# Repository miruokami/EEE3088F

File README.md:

# Micro-mouse Project
## Project Overview
The Micro-mouse project focuses on designing and building subassemblies for a simplified micro-mouse, a maze-solving robot. 
This project involves creating hardware components with some minor software aspects, adhering to a strict budget.

## Project Modules
### Provided Modules
Motherboard: Connects all the PCBs together, serving as the base for other modules.
Processor: A STM32xxx processor board.

### Modules to Design and Manufacture
#### Power Module:
Responsibilities: Powering the entire system, running the motors, and charging the battery.
Requirements: Fit onto the motherboard pin headers, appropriate size for the robot, includes necessary connectors (e.g., JST PH 2mm pitch for the battery, 2x8 pin header for motherboard connection).

#### Sensor Module:
Responsibilities: Detecting and sensing objects.
Requirements: Fit onto the motherboard pin headers, appropriate size for the robot, utilize hysteresis for sensing, accurately sense different maze wall configurations.

## Demonstration Procedures
### Sensing Subsystem
Preparation: Bring a PCB, code ready to flash onto the STM32F0, and populated PCB.
Setup: Flash code, connect the necessary wires, plug sensing PCB into the testing PCB.
Testing: The sensor is supplied with power, and walls will be moved in various configurations to test the sensing accuracy.

### Power Subsystem
Preparation: Bring a PCB, and 4 spare PCBs.
Setup: Plug power PCB into the testing jig.

This README provides a concise overview of the Micro-mouse project, including project modules, and demonstration procedures. 
For comprehensive guidelines, please refer to the provided project description document .

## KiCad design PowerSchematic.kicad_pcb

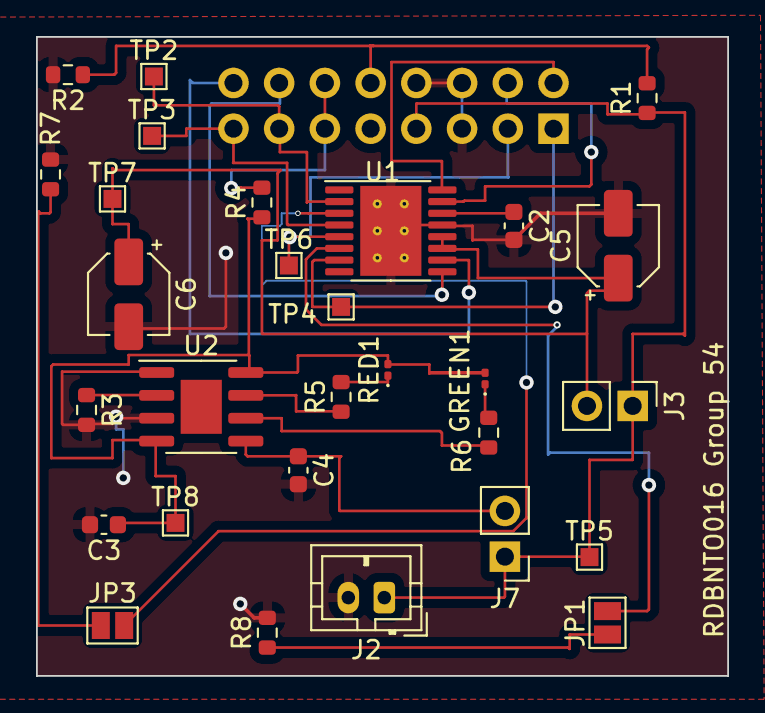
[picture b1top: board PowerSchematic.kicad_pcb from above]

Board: 2 copper layers, 38.4 x 35.5 mm, 30 parts (1 on the bottom side), 25 nets.

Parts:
C2: 2.2uF; C_0603_1608Metric
C3: 100nF; C_0603_1608Metric
C4: 10uF; C_0603_1608Metric
C5: 10uF; CP_Elec_4x3
C6: 0.01uF; CP_Elec_4x3
GREEN1: LED; LED_0201_0603Metric
J1: Conn_02x08_Odd_Even; PinHeader_2x08_P2.54mm_Vertical
J2: Battery; JST_PH_B2B-PH-K_1x02_P2.00mm_Vertical
J3, J7: Conn_01x02_Pin; PinHeader_1x02_P2.54mm_Vertical
JP1, JP3: SolderJumper_2_Open; SolderJumper-2_P1.3mm_Open_Pad1.0x1.5mm
R1: 10k; R_0603_1608Metric
R2: 5k; R_0603_1608Metric
R3: 1.2k; R_0603_1608Metric
R4: 0.4; R_0603_1608Metric
R5, R6: 1k; R_0603_1608Metric
R7, R8: 1; R_0603_1608Metric
RED1: LED; LED_0201_0603Metric
TP2, TP3, TP4, TP5, TP6, TP7, TP8: TestPoint; TestPoint_Pad_1.0x1.0mm
U1: DRV8833PWP; HTSSOP-16-1EP_4.4x5mm_P0.65mm_EP3.4x5mm_Mask2.46x2.31mm_The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
U2: TP4056; SOIC-8-1EP_3.9x4.9mm_P1.27mm_EP2.29x3mm

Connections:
5V: J1.11, J1.12, R4.2
BATT+: J1.7, J2.1, J3.1, J7.1, R1.1, TP5.1
BATT-: C2.2, C3.2, C4.2, C5.2, C6.2, J1.5, J1.6, J1.8, J2.2, R2.2, R3.2, R7.2, R8.2, U1.13 (GND), U1.17 (GND(PPAD)), U2.1 (TEMP), U2.3 (GND)
BATT_ADC: J1.10, R1.2, R2.1
Motor1_A: J1.13, TP2.1, U1.2 (AOUT1)
Motor1_B: J1.15, TP3.1, U1.4 (AOUT2)
Motor2_A: J1.1, TP4.1, U1.7 (BOUT1)
Motor2_B: J1.3, TP6.1, U1.5 (BOUT2)
unnamed: C3.1, GREEN1.2 (A), R4.1, RED1.2 (A), TP8.1, U2.4 (VCC), U2.8 (CE)
unnamed: GREEN1.1 (K), R6.2
unnamed: C4.1, J7.2, U2.5 (BAT)
unnamed: JP1.1 (A), R8.1
unnamed: JP1.2 (B), U1.6 (BISEN)
unnamed: JP3.1 (A), R7.1
unnamed: JP3.2 (B), U1.3 (AISEN)
unnamed: R5.2, RED1.1 (K)
unnamed: C2.1, U1.14 (VINT)
unnamed: R3.1, U2.2 (PROG)
unnamed: R5.1, U2.7 (~CHRG)
unnamed: R6.1, U2.6 (~STDBY)
PC6: J1.2, U1.16 (AIN1)
PC7: J1.4, U1.15 (AIN2)
PC8: J1.14, U1.9 (BIN1)
PC9: J1.16, U1.10 (BIN2)
VM: C5.1, C6.1, J3.2, TP7.1, U1.11 (VCP), U1.12 (VM)

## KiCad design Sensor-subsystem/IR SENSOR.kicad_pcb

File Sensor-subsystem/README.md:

# Robot Sensor Subsystem
## Overview
This repository contains the design, implementation, and integration details of the sensor subsystem for a robot project. The sensor subsystem is responsible for detecting obstacles in front, to the left, and to the right of the robot, providing essential information for navigation and obstacle avoidance.

## Features
Obstacle Detection: Uses IR sensors to detect obstacles in three directions: front, left, and right.
Power Management: Implements MOSFET switches to enable/disable sensors, conserving battery power when sensors are not in use.
Visual Indication: Uses LEDs on the processor board to indicate the presence of obstacles.
High Reliability: Designed with redundant ground planes, decoupling capacitors, and other failure management processes to ensure robust operation.

## System Integration
The sensor subsystem integrates with the main robot system through a 2x14 pin header connection. It interfaces with the robot's processor to provide obstacle detection data and receive power management signals.

## Power Management
To ensure efficient power usage, the subsystem employs MOSFET switches controlled by PWM signals from the processor. This allows the sensors to be powered only when needed, conserving battery life.

## Components
IR Sensors: Detect obstacles by emitting and detecting infrared light.
MOSFETs: Switch the power supply to the sensors on and off.
Microcontroller: Reads sensor data and controls MOSFETs and LEDs.
LEDs: Indicate the presence of obstacles.

## Software
The software interfaces the sensor subsystem with the rest of the robot's system, handling sensor readings, power management, and LED indications.

## Getting Started
Hardware Setup: Assemble the sensor subsystem on the PCB and connect it to the robot's processor board using the 2x14 pin header.
Software Setup: write code to the microcontroller to start interfacing with the sensors.
Testing: Use the LEDs to verify that the sensors are correctly detecting obstacles.

# License
This project is licensed under the MIT License - see the LICENSE file for details.

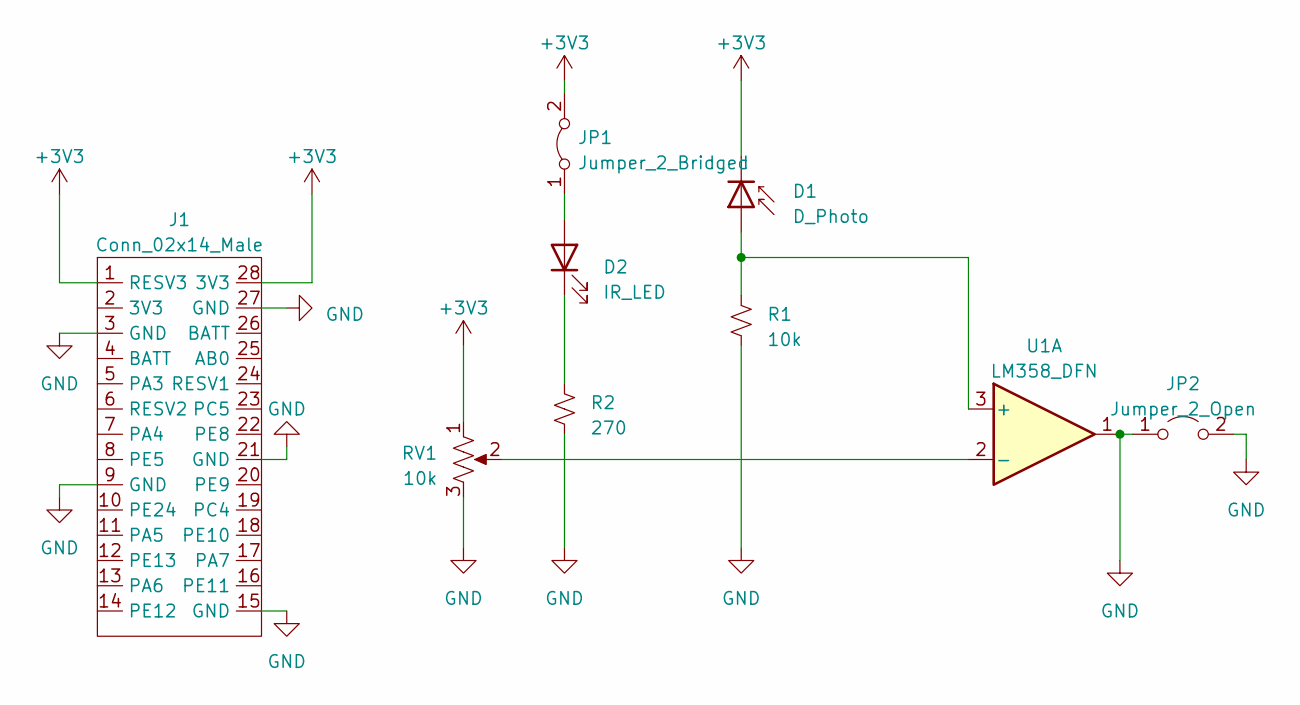
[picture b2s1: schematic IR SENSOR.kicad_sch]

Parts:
D1: D_Photo; LED_D5.0mm_Horizontal_O3.81mm_Z3.0mm
D2: IR_LED; LED_D5.0mm_Horizontal_O3.81mm_Z3.0mm
J1: Conn_02x14_Male; PinHeader_2x14_P2.54mm_Vertical
JP1: Jumper_2_Bridged; SolderJumper-2_P1.3mm_Bridged_RoundedPad1.0x1.5mm
JP2: Jumper_2_Open; SolderJumper-2_P1.3mm_Open_TrianglePad1.0x1.5mm
R1: 10k; R_Axial_DIN0204_L3.6mm_D1.6mm_P2.54mm_Vertical
R2: 270; R_Axial_DIN0204_L3.6mm_D1.6mm_P2.54mm_Vertical
RV1: 10k; Potentiometer_ACP_CA9-H2,5_Horizontal
U1: LM358_DFN; DFN-8-1EP_2x2mm_P0.5mm_EP1.05x1.75mm

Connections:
+3V3: D1.1 (K), J1.1 (RESV3), J1.28 (3V3), JP1.2 (B), RV1.1
GND: J1.3 (GND), J1.9 (GND), J1.15 (GND), J1.21 (GND), J1.27 (GND), JP2.1 (A), JP2.2 (B), R1.1, R2.1, RV1.3, U1.1
unnamed: D1.2 (A), R1.2, U1.3 (+)
unnamed: D2.2 (A), JP1.1 (A)
unnamed: D2.1 (K), R2.2
unnamed: RV1.2, U1.2 (-)

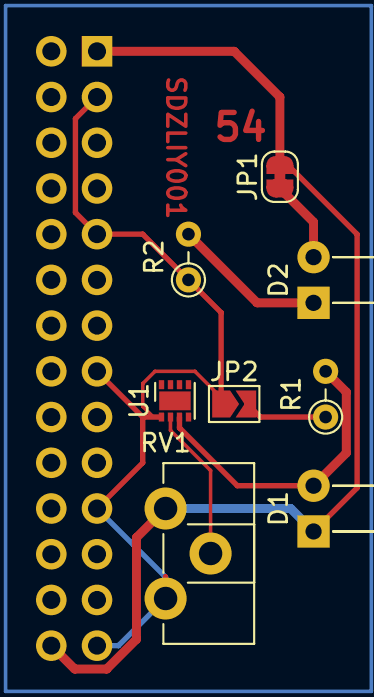
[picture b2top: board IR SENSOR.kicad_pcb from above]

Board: 2 copper layers, 9 parts (1 on the bottom side), 6 nets.

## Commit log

2024-04-21 Add files via upload
    Added all necessary documents.
2024-05-17 Moving files to sensor foulder
2024-05-17 deleted README.txt
2024-05-17 moving files to power foulder
